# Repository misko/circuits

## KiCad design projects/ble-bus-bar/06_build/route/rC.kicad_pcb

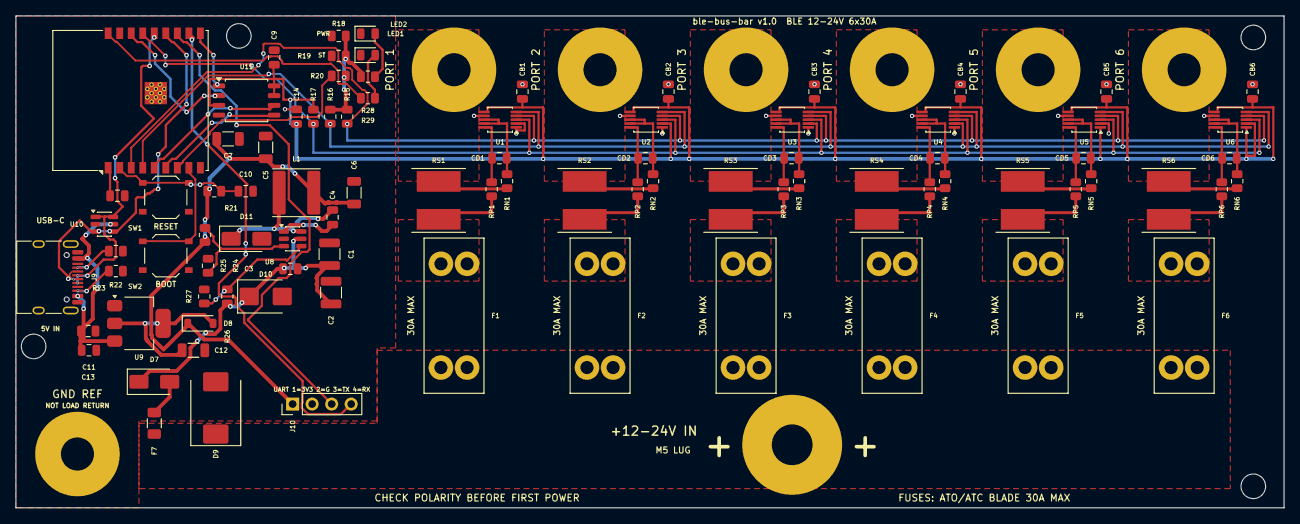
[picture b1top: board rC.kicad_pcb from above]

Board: 2 copper layers, 165.0 x 64.0 mm, 101 parts (0 on the bottom side), 55 nets.

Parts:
C1, C2: 4u7 50V; C_1210_3225Metric
C3: 100n VIN; C_0805_2012Metric
C4: 100n boot; C_0805_2012Metric
C5, C6: 22u 3V3; C_1206_3216Metric
C7: 22u U7; C_1206_3216Metric
C8: 100n U7; C_0805_2012Metric
C9: 100n U11; C_0805_2012Metric
C10: 1u EN; C_0805_2012Metric
C11: 10u LDO in; C_0805_2012Metric
C12: 22u LDO out; C_1206_3216Metric
C13: 100n VUSB; C_0805_2012Metric
C14: 100n corridor 3V3; C_0805_2012Metric
CB1, CB2, CB3, CB4, CB5, CB6: 100n INA; C_0805_2012Metric
CD1, CD2, CD3, CD4, CD5, CD6: 100n diff; C_0805_2012Metric
D7: SS310 rev block; D_SMA
D8: B5819W OR; D_SOD-123
D9: SMCJ33A bus TVS; D_SMC
D10: SMBJ33A tap TVS; D_SMB
D11: SS310 catch; D_SMA
F1, F2, F3, F4, F5, F6: 3557-2 ATO 30A MAX; FuseHolder_Keystone_3557-2
F7: 0466002 2A; Fuse_1206_3216Metric
H1, H2, H3, H4: MountingHole_3.2mm_M3
J1: PORT 1 M4 LUG; Lug_M4
J2: PORT 2 M4 LUG; Lug_M4
J3: PORT 3 M4 LUG; Lug_M4
J4: PORT 4 M4 LUG; Lug_M4
J5: PORT 5 M4 LUG; Lug_M4
J6: PORT 6 M4 LUG; Lug_M4
J7: +12-24V IN M5 LUG; Lug_M5
J8: GND REF M4 LUG; Lug_M4
J9: TYPE-C-31-M-12; USB_C_Receptacle_HRO_TYPE-C-31-M-12
J10: DEBUG UART DNP; PinHeader_1x04_P2.54mm_Vertical
L1: 22u SWPA6045S; L_Sunlord_SWPA6045S
LED1: KT-0805G PWR; LED_0805_2012Metric
LED2: KT-0805G ST; LED_0805_2012Metric
R15: 4k7 SDA pu; R_0805_2012Metric
R16: 4k7 SCL pu; R_0805_2012Metric
R17: 10k ALERT pu; R_0805_2012Metric
R18: 10k IO2 pu; R_0805_2012Metric
R19: 10k CS pu; R_0805_2012Metric
R20: 10k IO8 pu; R_0805_2012Metric
R21: 10k EN pu; R_0805_2012Metric
R22: 5k1 CC1; R_0805_2012Metric
R23: 5k1 CC2; R_0805_2012Metric
R24: 33k FB hi; R_0805_2012Metric
R25: 10k FB lo; R_0805_2012Metric
R26: 560k UVLO hi; R_0805_2012Metric
R27: 100k UVLO lo; R_0805_2012Metric
R28: 2k PWR LED; R_0805_2012Metric
R29: 1k ST LED; R_0805_2012Metric
RN1, RN2, RN3, RN4, RN5, RN6: 10R sense-; R_0805_2012Metric
RP1, RP2, RP3, RP4, RP5, RP6: 10R sense+; R_0805_2012Metric
RS1, RS2, RS3, RS4, RS5, RS6: WSLP2726 0.5mR; R_Shunt_WSLP2726
SW1: RESET; SW_Push_1P1T_XKB_TS-1187A
SW2: BOOT; SW_Push_1P1T_XKB_TS-1187A
U1, U2, U3, U4, U5, U6: INA238AIDGSR; MSOP-10_3x3mm_P0.5mm
U7: ESP32-C3-WROOM-02-N4; ESP32-C3-WROOM-02_D03
U8: LMR16006XDDCR; TSOT-23-6
U9: AMS1117-3.3; SOT-223-3_TabPin2
U10: USBLC6-2SC6; SOT-23-6
U11: W25Q64JVSSIQ; SOIC-8_5.3x5.3mm_P1.27mm

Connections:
3V3: C8.1, C9.1, CB1.1, CB2.1, CB3.1, CB4.1, CB5.1, CB6.1, U1.6, U2.2, U2.6, U3.6, U4.6, U5.1, U5.6, U6.1, U6.2, U6.6, U11.3, U11.7, U11.8
ALERT: R17.1, U1.3, U2.3, U3.3, U4.3, U5.3, U6.3, U7.15
BOOT: C4.1, U8.1
BOOT9: SW2.1, U7.8
CC1: J9.A5, R22.1
CC2: J9.B5, R23.1
EN: C10.1, R21.2, SW1.1, U7.2
FB: R24.2, R25.1, U8.3
FLASH_CS: R19.1, U7.10, U11.1
GND: C1.2, C2.2, C3.2, C5.2, C6.2, C7.2, C8.2, C9.2, C10.2, C11.2, C12.2, C13.2, C14.2, CB1.2, CB2.2, CB3.2, CB4.2, CB5.2, CB6.2, D9.2, D10.2, D11.2, J8.1, J9.A1, J9.A12, J9.B1, J9.B12, J9.SH, J10.2, LED1.1, LED2.1, R22.2, R23.2, R25.2, R27.2, SW1.2, SW2.2, U1.1, U1.2, U1.7, U2.1, U2.7, U3.1, U3.7, U4.1, U4.7, U5.2, U5.7, U6.7, U7.9, U7.19, U8.2, U9.1, U10.2, U11.4
IO8: R20.1, U7.7
KA1: CD1.1, RP1.2, U1.10
KA2: CD2.1, RP2.2, U2.10
KA3: CD3.1, RP3.2, U3.10
KA4: CD4.1, RP4.2, U4.10
KA5: CD5.1, RP5.2, U5.10
KA6: CD6.1, RP6.2, U6.10
KB1: CD1.2, RN1.2, U1.8, U1.9
KB2: CD2.2, RN2.2, U2.8, U2.9
KB3: CD3.2, RN3.2, U3.8, U3.9
KB4: CD4.2, RN4.2, U4.8, U4.9
KB5: CD5.2, RN5.2, U5.8, U5.9
KB6: CD6.2, RN6.2, U6.8, U6.9
LED1A: LED1.2, R28.2
LED2A: LED2.2, R29.2
LED_ST: R29.1, U7.18
RXD: J10.4, U7.11
SCL: R16.1, U1.5, U2.5, U3.5, U4.2, U4.5, U5.5, U6.5, U7.4
SDA: R15.1, U1.4, U2.4, U3.2, U3.4, U4.4, U5.4, U6.4, U7.3
SHDN: R26.2, R27.1, U8.4
SPI_CLK: U7.5, U11.6
SPI_MISO: R18.1, U7.16, U11.2
SPI_MOSI: U7.6, U11.5
SW: C4.2, D11.1, L1.1, U8.6
TMP_3V3: C5.1, C6.1, C7.1, C14.1, D8.1, J10.1, L1.2, R15.2, R16.2, R17.2, R18.2, R19.2, R20.2, R21.1, R24.1, R28.1, U7.1
TXD: J10.3, U7.12
USB_DM: J9.A7, J9.B7, U7.13, U10.3, U10.4
USB_DP: J9.A6, J9.B6, U7.14, U10.1, U10.6
VBUS: D9.1, F1.1, F2.1, F3.1, F4.1, F5.1, F6.1, F7.1, J7.1
VF1: F1.2, RP1.1, RS1.1
VF2: F2.2, RP2.1, RS2.1
VF3: F3.2, RP3.1, RS3.1
VF4: F4.2, RP4.1, RS4.1
VF5: F5.2, RP5.1, RS5.1
VF6: F6.2, RP6.1, RS6.1
VIN_E: C1.1, C2.1, C3.1, D7.1, D10.1, R26.1, U8.5
VLDO: C12.1, D8.2, U9.2
VP1: J1.1, RN1.1, RS1.2
VP2: J2.1, RN2.1, RS2.2
VP3: J3.1, RN3.1, RS3.2
VP4: J4.1, RN4.1, RS4.2
VP5: J5.1, RN5.1, RS5.2
VP6: J6.1, RN6.1, RS6.2
VTAP: D7.2, F7.2
VUSB: C11.1, C13.1, J9.A4, J9.A9, J9.B4, J9.B9, U9.3, U10.5

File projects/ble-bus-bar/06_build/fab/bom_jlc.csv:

Comment,Designator,Footprint,MPN,LCSC
0466002 2A,F7,Fuse_1206_3216Metric,0466002.NRHF,C3105
100k UVLO lo,R27,R_0805_2012Metric,0805W8F1003T5E,C149504
100n,"C13,C14,C3,C4,C8,C9,CB1,CB2,CB3,CB4,CB5,CB6,CD1,CD2,CD3,CD4,CD5,CD6",C_0805_2012Metric,CC0805KRX7R9BB104,C49678
10R,"RN1,RN2,RN3,RN4,RN5,RN6,RP1,RP2,RP3,RP4,RP5,RP6",R_0805_2012Metric,0805W8F100JT5E,C17415
10k,"R17,R18,R19,R20,R21,R25",R_0805_2012Metric,0805W8F1002T5E,C17414
10u LDO in,C11,C_0805_2012Metric,CL21A106KAYNNNE,C15850
1k ST LED,R29,R_0805_2012Metric,0805W8F1001T5E,C17513
1u EN,C10,C_0805_2012Metric,CL21B105KBFNNNE,C28323
22u,"C12,C5,C6,C7",C_1206_3216Metric,CL31A226KAHNNNE,C12891
22u SWPA6045S,L1,L_Sunlord_SWPA6045S,SWPA6045S220MT,C83454
2k PWR LED,R28,R_0805_2012Metric,0805W8F2001T5E,C17604
33k FB hi,R24,R_0805_2012Metric,0805W8F3302T5E,C17633
3557-2 ATO 30A MAX,"F1,F2,F3,F4,F5,F6",FuseHolder_Keystone_3557-2,3557-2,
4k7,"R15,R16",R_0805_2012Metric,0805W8F4701T5E,C17673
4u7 50V,"C1,C2",C_1210_3225Metric,GRM32ER71H475KA88L,C86052
560k UVLO hi,R26,R_0805_2012Metric,0805W8F5603T5E,C15785
5k1,"R22,R23",R_0805_2012Metric,0805W8F5101T5E,C27834
AMS1117-3.3,U9,SOT-223-3_TabPin2,AMS1117-3.3,C6186
B5819W OR,D8,D_SOD-123,B5819W,C8598
BOOT / RESET,"SW1,SW2",SW_Push_1P1T_XKB_TS-1187A,TS-1187A-B-A-B,C318884
ESP32-C3-WROOM-02-N4,U7,ESP32-C3-WROOM-02_D03,ESP32-C3-WROOM-02-N4,C2934560
INA238AIDGSR,"U1,U2,U3,U4,U5,U6",MSOP-10_3x3mm_P0.5mm,INA238AIDGSR,C2868250
KT-0805G,"LED1,LED2",LED_0805_2012Metric,KT-0805G,C2297
LMR16006XDDCR,U8,TSOT-23-6,LMR16006XDDCR,C87080
SMBJ33A tap TVS,D10,D_SMB,SMBJ33A,C173526
SMCJ33A bus TVS,D9,D_SMC,SMCJ33A,C152083
SS310,"D11,D7",D_SMA,SS310,C15874
TYPE-C-31-M-12,J9,USB_C_Receptacle_HRO_TYPE-C-31-M-12,TYPE-C-31-M-12,C165948
USBLC6-2SC6,U10,SOT-23-6,USBLC6-2SC6,C2687116
W25Q64JVSSIQ,U11,SOIC-8_3.9x4.9mm_P1.27mm,W25Q64JVSSIQ,C179171
WSLP2726 0.5mR,"RS1,RS2,RS3,RS4,RS5,RS6",R_Shunt_WSLP2726,WSLP2726L5000FEA,C844297

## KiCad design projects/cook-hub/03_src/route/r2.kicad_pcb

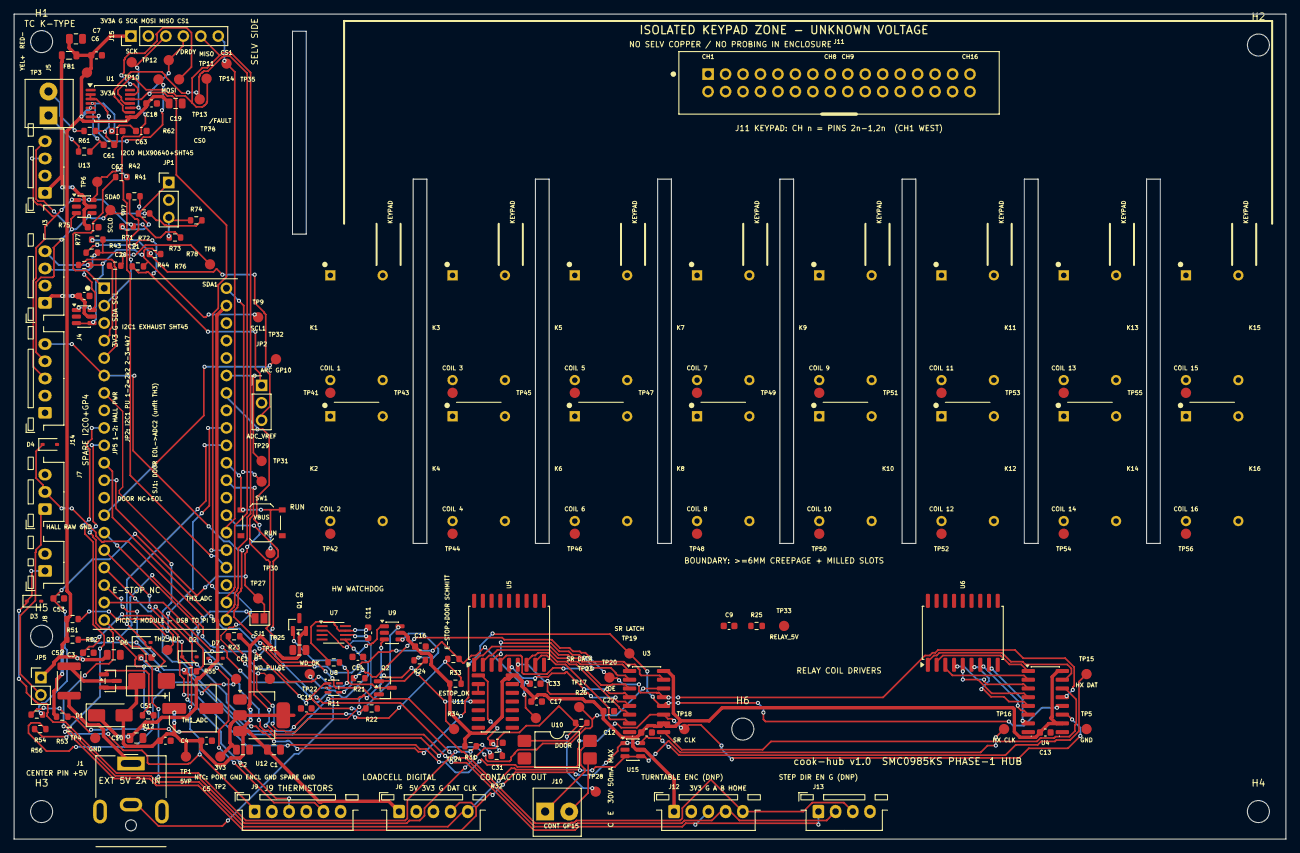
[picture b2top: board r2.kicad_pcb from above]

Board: 4 copper layers, 185.0 x 120.0 mm, 182 parts (0 on the bottom side), 135 nets.

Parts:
C1: 10u LDO in; C_0805_2012Metric
C2, C3: 22u 3V3; C_0805_2012Metric
C4, C5: 22u 5VP; C_0603_1608Metric
C6: 10u 3V3A; C_0805_2012Metric
C7: 100n 3V3A; C_0603_1608Metric
C8: 10u RELAY_5V; C_0805_2012Metric
C9: 100n RELAY_5V; C_0603_1608Metric
C10: 10u VSYS; C_0805_2012Metric
C11: 1u X7R WD; C_0603_1608Metric
C12: 100n U3; C_0603_1608Metric
C13: 100n U4; C_0603_1608Metric
C14: 100n U7; C_0603_1608Metric
C15: 100n U8; C_0603_1608Metric
C16: 100n U9; C_0603_1608Metric
C17: 100n U11; C_0603_1608Metric
C18: 100n U1; C_0603_1608Metric
C19: 10u U1; C_0805_2012Metric
C20: 100n U13; C_0603_1608Metric
C21: 100n U14; C_0603_1608Metric
C22: 100n U15; C_0603_1608Metric
C31: 100n estop RC; C_0603_1608Metric
C33: 100n door RC; C_0603_1608Metric
C51, C52, C53: 100n RC; C_0603_1608Metric
C61: 100n TC diff; C_0603_1608Metric
C62: 10n TC+ cm; C_0603_1608Metric
C63: 10n TC- cm; C_0603_1608Metric
CE1: 220u 16V bulk; CP_Elec_6.3x7.7
D1: SS34 VSYS OR; D_SMA
D2: SMBJ5.0A; D_SMB
D3, D4, D5, D6, D7: PESD5V0S1BA; D_SOD-323
F1: MF-MSMF200L 2A; Fuse_1812_4532Metric
FB1: 600R ferrite; L_0805_2012Metric
H1, H2, H3, H4, H5, H6: MountingHole_3.2mm_M3
J1: EXT 5V 2A; BarrelJack_CUI_PJ-063AH_Horizontal
J2: Pico 2 socket; Pico2_Socket_2x20
J3: I2C0 MLX+SHT45; JST_XH_B4B-XH-A_1x04_P2.50mm_Vertical
J4: I2C1 EXHAUST SHT45; JST_XH_B4B-XH-A_1x04_P2.50mm_Vertical
J5: TC K-TYPE; TerminalBlock_KF350_2P
J6: LOADCELL DIG; JST_XH_B5B-XH-A_1x05_P2.50mm_Vertical
J7: DOOR NC+EOL; JST_XH_B3B-XH-A_1x03_P2.50mm_Vertical
J8: E-STOP NC; JST_XH_B2B-XH-A_1x02_P2.50mm_Vertical
J9: NTC x3; JST_XH_B6B-XH-A_1x06_P2.50mm_Vertical
J10: CONTACTOR 30V; TerminalBlock_KF350_2P
J11: X9555WV 2x16 KEYPAD; IDC_2x16_Keyed
J12: ENCODER DNP; JST_XH_B5B-XH-A_1x05_P2.50mm_Vertical
J13: STEP/DIR/EN DNP; JST_XH_B4B-XH-A_1x04_P2.50mm_Vertical
J14: SPARE I2C0+GP4; JST_XH_B5B-XH-A_1x05_P2.50mm_Vertical
J15: MAX31865 DNP; PinHeader_1x06_P2.54mm_Vertical
JP1: I2C0 PU 2k2|4k7; PinHeader_1x03_P2.54mm_Vertical
JP2: I2C1 PU 2k2|4k7; PinHeader_1x03_P2.54mm_Vertical
JP5: HALL 3V3 opt; PinHeader_1x02_P2.54mm_Vertical
K1, K2, K3, K4, K5, K6, K7, K8, K9, K10, K11, K12, K13, K14, K15, K16: DIP05-1A72-12L; Relay_StandexDIP_1A_pinout12
Q1: AO3401A hi-side; SOT-23
Q2: 2N7002; SOT-23
Q3: AO3401A rev-prot; SOT-23
R11: 390k 1% WD; R_0603_1608Metric
R12: 100k Q3 gate; R_0603_1608Metric
R21: 10k /OE pu; R_0603_1608Metric
R22: 10k RLY_EN pd; R_0603_1608Metric
R23: 47k Q1 pu; R_0603_1608Metric
R24: 1k Q2 gate; R_0603_1608Metric
R25: 10k bleed; R_0603_1608Metric
R26: 330R opto LED; R_0603_1608Metric
R31: 3k3 estop pu; R_0603_1608Metric
R32: 10k estop RC; R_0603_1608Metric
R33: 3k3 door pu; R_0603_1608Metric
R34: 10k door RC; R_0603_1608Metric
R41: 33R SDA0; R_0603_1608Metric
R42: 33R SCL0; R_0603_1608Metric
R43: 33R SDA1; R_0603_1608Metric
R44: 33R SCL1; R_0603_1608Metric
R51, R52, R53: 10k 1% ref; R_0603_1608Metric
R54, R55, R56: 1k RC; R_0603_1608Metric
R61: 100R TC+; R_0603_1608Metric
R62: 100R TC-; R_0603_1608Metric
R71: 2k2 SDA0 pu; R_0603_1608Metric
R72: 2k2 SCL0 pu; R_0603_1608Metric
R73: 4k7 SDA0 pu; R_0603_1608Metric
R74: 4k7 SCL0 pu; R_0603_1608Metric
R75: 2k2 SDA1 pu; R_0603_1608Metric
R76: 2k2 SCL1 pu; R_0603_1608Metric
R77: 4k7 SDA1 pu; R_0603_1608Metric
R78: 4k7 SCL1 pu; R_0603_1608Metric
SJ1: DOOR->ADC2 opt; SolderJumper-2_P1.3mm_Open_Pad1.0x1.5mm
SW1: RUN reset; SW_Push_1P1T_XKB_TS-1187A
TP1: TP 5VP; TestPoint_Pad_D1.5mm
TP2: TP 3V3; TestPoint_Pad_D1.5mm
TP3: TP 3V3A; TestPoint_Pad_D1.5mm
TP4, TP5: TP GND; TestPoint_Pad_D1.5mm
TP6: TP SDA0; TestPoint_Pad_D1.5mm
TP7: TP SCL0; TestPoint_Pad_D1.5mm
TP8: TP SDA1; TestPoint_Pad_D1.5mm
TP9: TP SCL1; TestPoint_Pad_D1.5mm
TP10: TP SCK; TestPoint_Pad_D1.5mm
TP11: TP MISO; TestPoint_Pad_D1.5mm
TP12: TP MOSI; TestPoint_Pad_D1.5mm
TP13: TP CS0; TestPoint_Pad_D1.5mm
TP14: TP CS1; TestPoint_Pad_D1.5mm
TP15: TP HX DAT; TestPoint_Pad_D1.5mm
TP16: TP HX CLK; TestPoint_Pad_D1.5mm
TP17: TP SR DATA; TestPoint_Pad_D1.5mm
TP18: TP SR CLK; TestPoint_Pad_D1.5mm
TP19: TP SR LATCH; TestPoint_Pad_D1.5mm
TP20: TP /OE; TestPoint_Pad_D1.5mm
TP21: TP WD_PULSE; TestPoint_Pad_D1.5mm
TP22: TP WD_OK; TestPoint_Pad_D1.5mm
TP23: TP DOOR; TestPoint_Pad_D1.5mm
TP24: TP ESTOP_OK; TestPoint_Pad_D1.5mm
TP25: TP TH1_ADC; TestPoint_Pad_D1.5mm
TP26: TP TH2_ADC; TestPoint_Pad_D1.5mm
TP27: TP TH3_ADC; TestPoint_Pad_D1.5mm
TP28: TP CONT GP15; TestPoint_Pad_D1.5mm
TP29: TP VBUS; TestPoint_Pad_D1.5mm
TP30: TP RUN; TestPoint_Pad_D1.5mm
TP31: TP ADC_VREF; TestPoint_Pad_D1.5mm
TP32: TP ARC GP10; TestPoint_Pad_D1.5mm
TP33: TP RELAY_5V; TestPoint_Pad_D1.5mm
TP34: TP /DRDY; TestPoint_Pad_D1.5mm
TP35: TP /FAULT; TestPoint_Pad_D1.5mm
TP41: TP COIL 1; TestPoint_Pad_D1.5mm
TP42: TP COIL 2; TestPoint_Pad_D1.5mm
TP43: TP COIL 3; TestPoint_Pad_D1.5mm
TP44: TP COIL 4; TestPoint_Pad_D1.5mm
TP45: TP COIL 5; TestPoint_Pad_D1.5mm
TP46: TP COIL 6; TestPoint_Pad_D1.5mm
TP47: TP COIL 7; TestPoint_Pad_D1.5mm
TP48: TP COIL 8; TestPoint_Pad_D1.5mm
TP49: TP COIL 9; TestPoint_Pad_D1.5mm
TP50: TP COIL 10; TestPoint_Pad_D1.5mm
TP51: TP COIL 11; TestPoint_Pad_D1.5mm
TP52: TP COIL 12; TestPoint_Pad_D1.5mm
TP53: TP COIL 13; TestPoint_Pad_D1.5mm
TP54: TP COIL 14; TestPoint_Pad_D1.5mm
TP55: TP COIL 15; TestPoint_Pad_D1.5mm
TP56: TP COIL 16; TestPoint_Pad_D1.5mm
U1: MAX31856; TSSOP-14_4.4x5mm_P0.65mm
U3: 74HC595 #1; SOIC-16_3.9x9.9mm_P1.27mm
U4: 74HC595 #2; SOIC-16_3.9x9.9mm_P1.27mm
U5: ULN2803A K1-K8; SOIC-18W_7.5x11.6mm_P1.27mm
U6: ULN2803A K9-K16; SOIC-18W_7.5x11.6mm_P1.27mm
U7: SN74LVC1G123; SSOP-8_2.95x2.8mm_P0.65mm
U8: 74LVC1G00 /OE; SOT-353_SC-70-5
U9: 74LVC1G11 AND3; SOT-23-6
U10: LTV-817S; SMDIP-4_W9.53mm
U11: 74HC14 E-stop; SOIC-14_3.9x8.7mm_P1.27mm
U12: AMS1117-3.3; SOT-223-3_TabPin2
U13, U14, U15: USBLC6-2SC6; SOT-23-6

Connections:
3V3: C2.1, C3.1, C12.1, C13.1, C14.1, C15.1, C16.1, C17.1, C20.1, C21.1, C22.1, FB1.1, J3.1, J4.1, J6.2, J12.1, J14.1, JP1.2, JP2.2, JP5.1, R11.2, R21.2, R31.1, R33.1, TP2.1, U3.10, U3.16, U4.10, U4.16, U7.3, U7.8, U8.5, U9.5, U11.14, U12.2, U13.5, U14.5, U15.5
3V3A: C6.1, C7.1, C18.1, C19.1, FB1.2, J15.1, R51.1, R52.1, R53.1, TP3.1, U1.5, U1.8
5VP: C1.1, C4.1, C5.1, CE1.1, D1.2, D2.1, J6.1, Q1.2, Q3.2, R23.2, TP1.1, U12.3
5V_D: F1.2, Q3.3
5V_IN: F1.1, J1.1
ADC_VREF: J2.35, TP31.1
ARC: J2.14, TP32.1
COIL_1: K1.7, TP41.1, U5.18
COIL_2: K2.7, TP42.1, U5.17
COIL_3: K3.7, TP43.1, U5.16
COIL_4: K4.7, TP44.1, U5.15
COIL_5: K5.7, TP45.1, U5.14
COIL_6: K6.7, TP46.1, U5.13
COIL_7: K7.7, TP47.1, U5.12
COIL_8: K8.7, TP48.1, U5.11
COIL_9: K9.7, TP49.1, U6.18
COIL_10: K10.7, TP50.1, U6.17
COIL_11: K11.7, TP51.1, U6.16
COIL_12: K12.7, TP52.1, U6.15
COIL_13: K13.7, TP53.1, U6.14
COIL_14: K14.7, TP54.1, U6.13
COIL_15: K15.7, TP55.1, U6.12
COIL_16: K16.7, TP56.1, U6.11
COIL_EN: R24.1, U9.4
CONT_A: R26.2, U10.1
CONT_C: J10.1, U10.4
CONT_E: J10.2, U10.3
CONT_REQ: J2.20, R26.1, TP28.1
CS0: J2.22, TP13.1, U1.9
CS1: J2.26, J15.6, TP14.1
DOOR_IN: C33.1, J2.11, R34.2, TP23.1
DOOR_RAW: D4.1, J7.2, R33.2, R34.1, SJ1.1
DRDY_N: TP34.1, U1.7
DRV1: U3.15, U5.1
DRV2: U3.1, U5.2
DRV3: U3.2, U5.3
DRV4: U3.3, U5.4
DRV5: U3.4, U5.5
DRV6: U3.5, U5.6
DRV7: U3.6, U5.7
DRV8: U3.7, U5.8
DRV9: U4.15, U6.1
DRV10: U4.1, U6.2
DRV11: U4.2, U6.3
DRV12: U4.3, U6.4
DRV13: U4.4, U6.5
DRV14: U4.5, U6.6
DRV15: U4.6, U6.7
DRV16: U4.7, U6.8
ESTOP_F: C31.1, R32.2, U11.1
ESTOP_INV: U11.2, U11.3
ESTOP_OK: J2.12, TP24.1, U9.3, U11.4
ESTOP_RAW: D3.1, J8.1, R31.2, R32.1
FAULT_N: TP35.1, U1.13
GND: C1.2, C2.2, C3.2, C4.2, C5.2, C6.2, C7.2, C8.2, C9.2, C10.2, C12.2, C13.2, C14.2, C15.2, C16.2, C17.2, C18.2, C19.2, C20.2, C21.2, C22.2, C31.2, C33.2, C51.2, C52.2, C53.2, C62.2, C63.2, CE1.2, D2.2, D3.2, D4.2, D5.2, D6.2, D7.2, J1.2, J2.3, J2.8, J2.13, J2.18, J2.23, J2.28, J2.33, J2.38, J3.2, J4.2, J6.3, J7.3, J8.2, J9.2, J9.4, J9.6, J12.2, J13.4, J14.2, J15.2, Q2.2, R12.2, R22.2, R25.2, SW1.2, TP4.1, TP5.1, U1.1, U1.14, U3.8, U4.8, U5.9, U6.9, U7.1, U7.4, U8.3, U9.2, U10.2, U11.5, U11.7, U11.9, U11.11, U11.13, U12.1, U13.2, U14.2, U15.2
GP4_SPARE: J2.6, J12.5, J13.3, J14.5
HALL_PWR: J7.1, JP5.2
HX_CLK: J2.10, J6.5, TP16.1, U15.3, U15.4
HX_DAT: J2.9, J6.4, TP15.1, U15.1, U15.6
KC1A: J11.1, K1.14
KC1B: J11.2, K1.8
KC2A: J11.3, K2.14
KC2B: J11.4, K2.8
KC3A: J11.5, K3.14
KC3B: J11.6, K3.8
KC4A: J11.7, K4.14
KC4B: J11.8, K4.8
KC5A: J11.9, K5.14
KC5B: J11.10, K5.8
KC6A: J11.11, K6.14
KC6B: J11.12, K6.8
KC7A: J11.13, K7.14
KC7B: J11.14, K7.8
KC8A: J11.15, K8.14
KC8B: J11.16, K8.8
KC9A: J11.17, K9.14
KC9B: J11.18, K9.8
KC10A: J11.19, K10.14
KC10B: J11.20, K10.8
KC11A: J11.21, K11.14
KC11B: J11.22, K11.8
KC12A: J11.23, K12.14
KC12B: J11.24, K12.8
KC13A: J11.25, K13.14
KC13B: J11.26, K13.8
KC14A: J11.27, K14.14
KC14B: J11.28, K14.8
KC15A: J11.29, K15.14
KC15B: J11.30, K15.8
KC16A: J11.31, K16.14
KC16B: J11.32, K16.8
MISO: J2.21, J15.5, TP11.1, U1.11
MOSI: J2.25, J15.4, TP12.1, U1.12
OE_N: R21.1, TP20.1, U3.13, U4.13, U8.4
PU0_22: JP1.1, R71.1, R72.1
PU0_47: JP1.3, R73.1, R74.1
PU1_22: JP2.1, R75.1, R76.1
PU1_47: JP2.3, R77.1, R78.1
Q1G: Q1.1, Q2.3, R23.1
Q2G: Q2.1, R24.2
Q3G: Q3.1, R12.1
RELAY_5V: C8.1, C9.1, K1.1, K2.1, K3.1, K4.1, K5.1, K6.1, K7.1, K8.1, K9.1, K10.1, K11.1, K12.1, K13.1, K14.1, K15.1, K16.1, Q1.3, R25.1, TP33.1, U5.10, U6.10
RLY_EN: J2.19, R22.1, U8.1, U9.6
RUN: J2.30, SW1.1, TP30.1
SCK: J2.24, J15.3, TP10.1, U1.10
SCL0: J2.2, R42.1
SCL0_J: J3.4, J14.4, R42.2, R72.2, R74.2, TP7.1, U13.3, U13.4
SCL1: J2.5, R44.1
SCL1_J: J4.4, R44.2, R76.2, R78.2, TP9.1, U14.3, U14.4
SDA0: J2.1, R41.1
SDA0_J: J3.3, J14.3, R41.2, R71.2, R73.2, TP6.1, U13.1, U13.6
SDA1: J2.4, R43.1
SDA1_J: J4.3, R43.2, R75.2, R77.2, TP8.1, U14.1, U14.6
SR_CASC: U3.9, U4.14
SR_CLK: J2.16, TP18.1, U3.11, U4.11
SR_DATA: J2.15, TP17.1, U3.14
SR_LATCH: J2.17, TP19.1, U3.12, U4.12
TC_MINUS_J: J5.2, R62.1
TC_N: C61.2, C63.1, R62.2, U1.2, U1.3
TC_P: C61.1, C62.1, R61.2, U1.4
TC_PLUS_J: J5.1, R61.1
TH1: D5.1, J9.1, R51.2, R54.1
TH1_ADC: C51.1, J2.31, R54.2, TP25.1
TH2: D6.1, J9.3, R52.2, R55.1
TH2_ADC: C52.1, J2.32, R55.2, TP26.1
TH3: D7.1, J9.5, R53.2, R56.1
TH3_ADC: C53.1, J2.34, R56.2, SJ1.2, TP27.1
TT_A: J2.27, J12.3, J13.1
TT_B: J2.29, J12.4, J13.2
VBUS_PICO: J2.40, TP29.1
VSYS: C10.1, D1.1, J2.39
WD_CX: C11.1, U7.6
WD_OK: TP22.1, U7.5, U8.2, U9.1
WD_PULSE: J2.7, TP21.1, U7.2
WD_RCX: C11.2, R11.1, U7.7
